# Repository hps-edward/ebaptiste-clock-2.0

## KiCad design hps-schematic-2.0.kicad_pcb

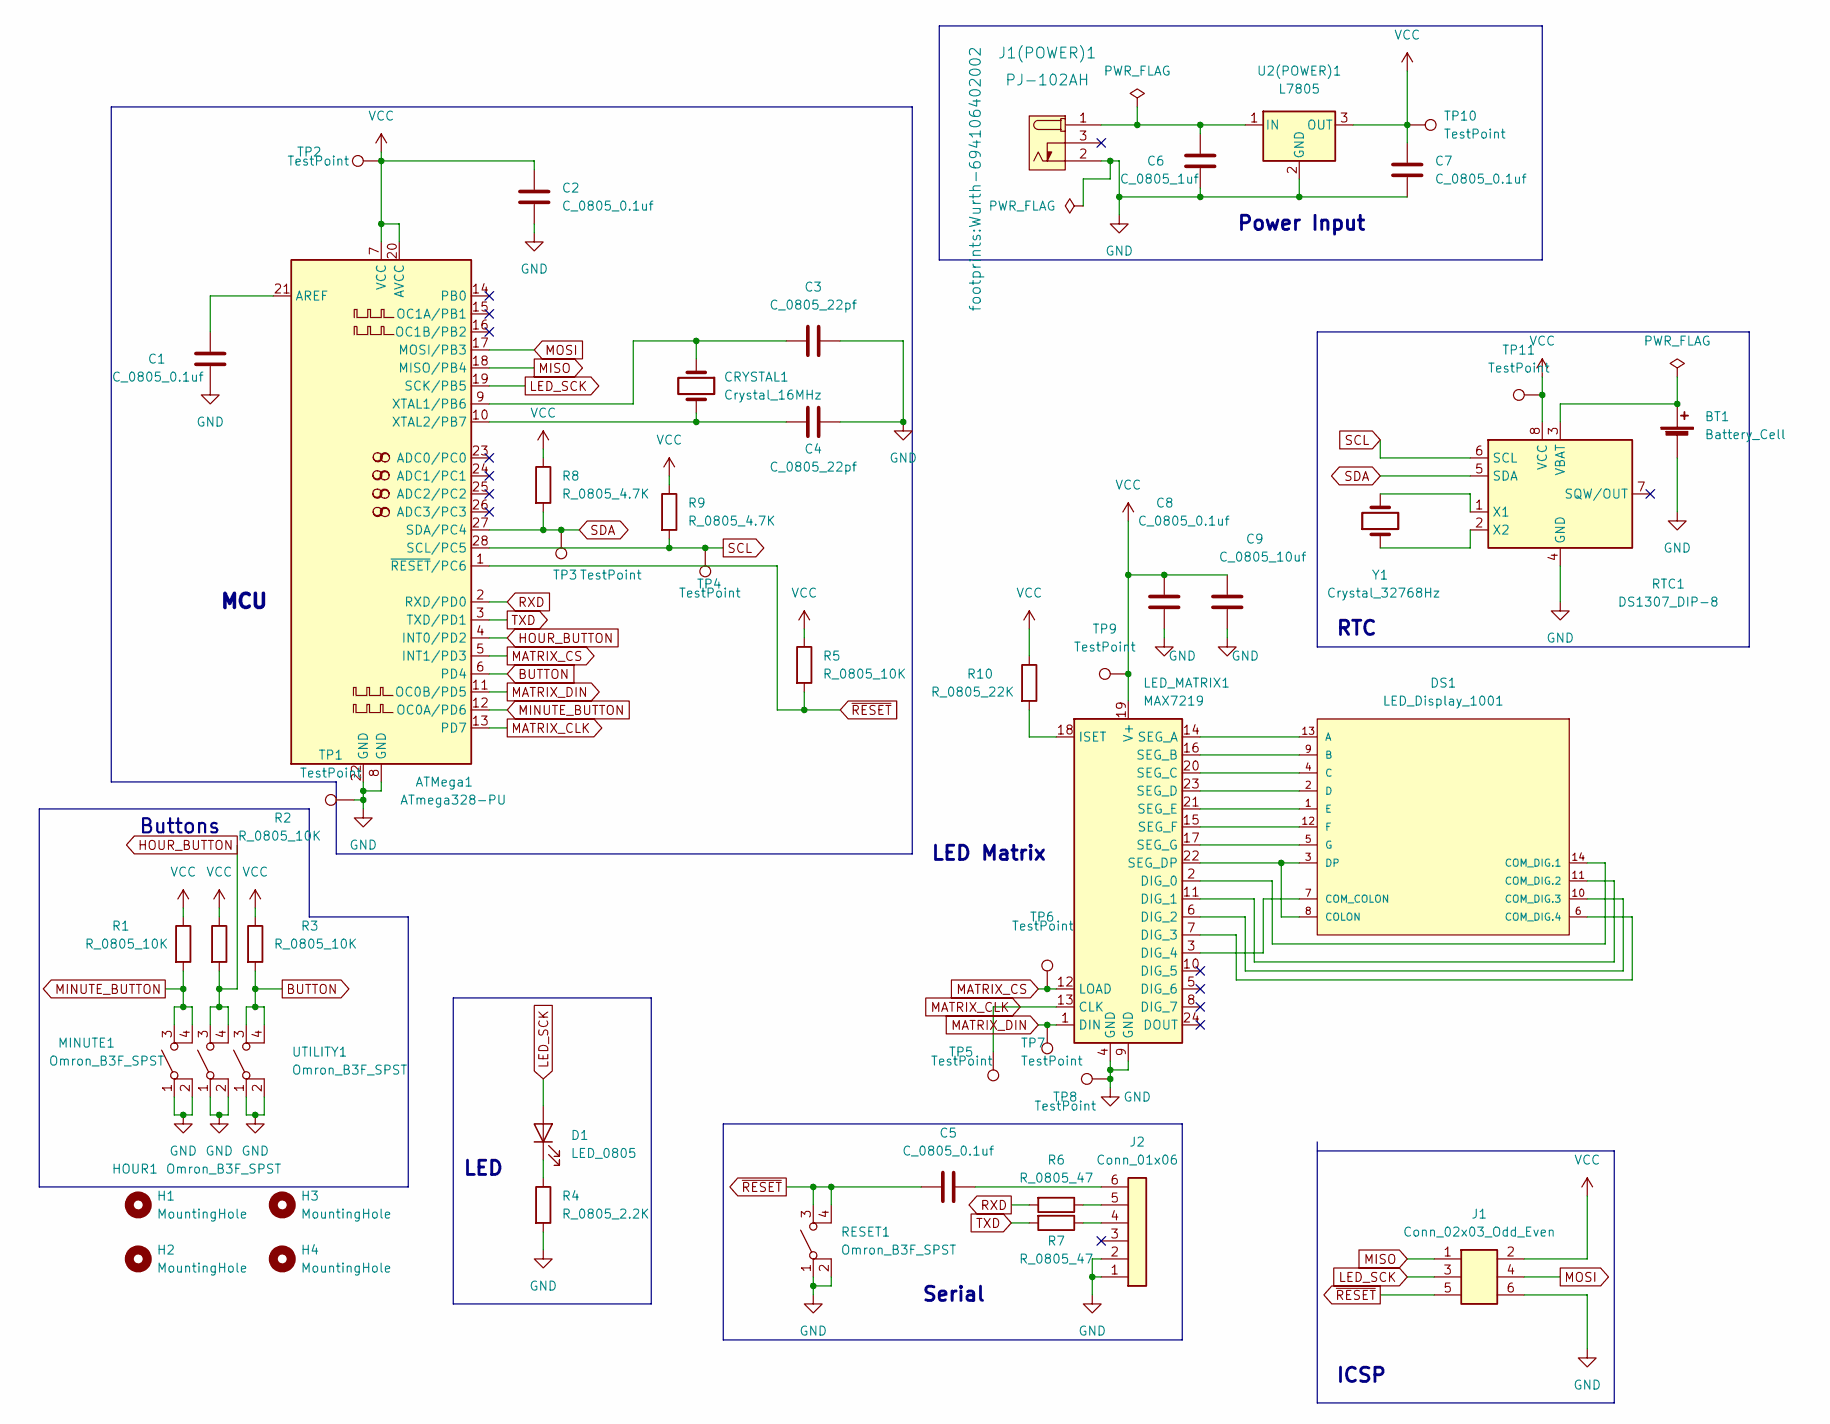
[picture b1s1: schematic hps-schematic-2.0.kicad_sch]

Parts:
ATMega1: ATmega328-PU; DIP-28_W7.62mm; MPN ED281DT; Digikey PN ED3050-5-ND
BT1: Battery_Cell; BatteryHolder_Keystone_106_1x20mm; MPN BS-7; Digikey PN BS-7-ND
C1, C2, C5, C7, C8: C_0805_0.1uf; C_0805_2012Metric; Voltage N/A; Tolerance N/A; MPN 08055C104KAT2A; Digikey PN 478-1395-1-ND
C3, C4: C_0805_22pf; C_0805_2012Metric; Voltage N/A; Tolerance N/A; MPN CC0805JRNPO9BN220; Digikey PN 311-1103-1-ND
C6: C_0805_1uf; C_0805_2012Metric; Voltage N/A; Tolerance N/A; MPN CC0805KKX7R8BB105; Digikey PN 311-1456-1-ND
C9: C_0805_10uf; C_0805_2012Metric; Voltage N/A; Tolerance N/A; MPN GRM21BR61E106KA73L; Digikey PN 490-5523-1-ND
CRYSTAL1: Crystal_16MHz; Crystal_SMD_HC49-SD; MPN ECS-160-20-5PXDN-TR; Digikey PN XC1299CT-ND
D1: LED_0805; LED_0805_2012Metric; MPN 150080RS75000; Digikey PN 732-4984-1-ND
DS1: LED_Display_1001; Adafruit-1001-0-0-MFG; forward voltage 3.2V; reverse voltage 5V; mouser part number 485-1001; digikey description WHITE 7-SEGMENT CLOCK DISPLAY
H1, H2, H3, H4: MountingHole; MountingHole_3.2mm_M3
HOUR1: Omron_B3F_SPST; SW_SPST_Omron_B3FS-100xP; MPN B3FS-1000P; Digikey PN SW423CT-ND
J1: Conn_02x03_Odd_Even; PinHeader_2x03_P2.54mm_Vertical; MPN PRPC003DAAN-RC; Digikey PN S2011EC-03-ND
J1(POWER)1: PJ-102AH; Wurth-694106402002; MPN 694106402002; Digikey PN 732-5931-ND
J2: Conn_01x06; PinHeader_1x06_P2.54mm_Vertical; MPN 61300611121; Digikey PN 732-5319-ND
LED_MATRIX1: MAX7219; DIP-24_W7.62mm; MPN ED241DT; Digikey PN ED3049-5-ND
MINUTE1: Omron_B3F_SPST; SW_SPST_Omron_B3FS-100xP; MPN B3FS-1000P; Digikey PN SW423CT-ND
R1, R2, R3, R5: R_0805_10K; R_0805_2012Metric; Tolerance N/A; MPN RC0805FR-0710KL; Digikey PN 311-10.0KCRCT-ND
R4: R_0805_2.2K; R_0805_2012Metric; Tolerance N/A; MPN N/A; Digikey PN 311-2.20KCRCT-ND
R6, R7: R_0805_47; R_0805_2012Metric; Tolerance N/A; Mouser PN N/A; Digikey PN RC0805FR-0747RL
R8, R9: R_0805_4.7K; R_0805_2012Metric; Tolerance N/A; MPN RC0805FR-074K7L; Digikey PN 311-4.70KCRCT-ND
R10: R_0805_22K; R_0805_2012Metric; Tolerance N/A; MPN RC0805FR-0722KL; Digikey PN 311-22.0KCRCT-ND
RESET1: Omron_B3F_SPST; SW_SPST_Omron_B3FS-100xP; MPN B3FS-1000P; Digikey PN SW423CT-ND
RTC1: DS1307_DIP-8; DIP-8_W7.62mm; MPN A 08-LC-TT; Digikey PN AE9986-ND
TP1, TP2, TP3, TP4, TP5, TP6, TP7, TP8, TP9, TP10, TP11: TestPoint; TestPoint_THTPad_D2.0mm_Drill1.0mm
U2(POWER)1: L7805; TO-252-2; MPN L7805CDT-TR; Digikey PN 497-7255-1-ND
UTILITY1: Omron_B3F_SPST; SW_SPST_Omron_B3FS-100xP; MPN B3FS-1000P; Digikey PN SW423CT-ND
Y1: Crystal_32768Hz; Crystal_SMD_2Pin_3.2x1.5mm; MPN Q 0,032768-JTX310-12,5-20-T1-HMR-50K-LF; Digikey PN 1908-1314-1-ND

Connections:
BUTTON: ATMega1.6 (PD4), R3.2, UTILITY1.3 (B), UTILITY1.4 (B)
GND: ATMega1.8 (GND), ATMega1.22 (GND), BT1.2 (-), C1.2, C2.2, C3.1, C4.1, C6.2, C7.2, C8.2, C9.2, HOUR1.1 (A), HOUR1.2 (A), J1.6, J1(POWER)1.2 (OUT), J2.1, J2.2, LED_MATRIX1.4 (GND), LED_MATRIX1.9 (GND), MINUTE1.1 (A), MINUTE1.2 (A), R4.2, RESET1.1 (A), RESET1.2 (A), RTC1.4 (GND), TP1.1, TP8.1, U2(POWER)1.2 (GND), UTILITY1.1 (A), UTILITY1.2 (A)
HOUR_BUTTON: ATMega1.4 (INT0/PD2), HOUR1.3 (B), HOUR1.4 (B), R2.2
LED_SCK: ATMega1.19 (SCK/PB5), D1.2 (A), J1.3
MATRIX_CLK: ATMega1.13 (PD7), LED_MATRIX1.13 (CLK), TP5.1
MATRIX_CS: ATMega1.5 (INT1/PD3), LED_MATRIX1.12 (LOAD), TP6.1
MATRIX_DIN: ATMega1.11 (OC0B/PD5), LED_MATRIX1.1 (DIN), TP7.1
MINUTE_BUTTON: ATMega1.12 (OC0A/PD6), MINUTE1.3 (B), MINUTE1.4 (B), R1.2
MISO: ATMega1.18 (MISO/PB4), J1.1
MOSI: ATMega1.17 (MOSI/PB3), J1.4
unnamed: ATMega1.9 (XTAL1/PB6), C3.2, CRYSTAL1.1
unnamed: ATMega1.10 (XTAL2/PB7), C4.2, CRYSTAL1.2
unnamed: ATMega1.21 (AREF), C1.1
unnamed: BT1.1 (+), RTC1.3 (VBAT)
unnamed: C5.2, J2.6
unnamed: C6.1, J1(POWER)1.1 (POLE), U2(POWER)1.1 (IN)
unnamed: D1.1 (K), R4.1
unnamed: DS1.1 (E), LED_MATRIX1.21 (SEG_E)
unnamed: DS1.2 (D), LED_MATRIX1.23 (SEG_D)
unnamed: DS1.3 (DP), DS1.8 (COLON), LED_MATRIX1.22 (SEG_DP)
unnamed: DS1.4 (C), LED_MATRIX1.20 (SEG_C)
unnamed: DS1.5 (G), LED_MATRIX1.17 (SEG_G)
unnamed: DS1.6 (COM_DIG.4), LED_MATRIX1.7 (DIG_3)
unnamed: DS1.7 (COM_COLON), LED_MATRIX1.3 (DIG_4)
unnamed: DS1.9 (B), LED_MATRIX1.16 (SEG_B)
unnamed: DS1.10 (COM_DIG.3), LED_MATRIX1.6 (DIG_2)
unnamed: DS1.11 (COM_DIG.2), LED_MATRIX1.11 (DIG_1)
unnamed: DS1.12 (F), LED_MATRIX1.15 (SEG_F)
unnamed: DS1.13 (A), LED_MATRIX1.14 (SEG_A)
unnamed: DS1.14 (COM_DIG.1), LED_MATRIX1.2 (DIG_0)
unnamed: J2.4, R7.1
unnamed: J2.5, R6.1
unnamed: LED_MATRIX1.18 (ISET), R10.2
unnamed: RTC1.1 (X1), Y1.2
unnamed: RTC1.2 (X2), Y1.1
RXD: ATMega1.2 (RXD/PD0), R6.2
SCL: ATMega1.28 (SCL/PC5), R9.2, RTC1.6 (SCL), TP4.1
SDA: ATMega1.27 (SDA/PC4), R8.2, RTC1.5 (SDA), TP3.1
TXD: ATMega1.3 (TXD/PD1), R7.2
VCC: ATMega1.7 (VCC), ATMega1.20 (AVCC), C2.1, C7.1, C8.1, C9.1, J1.2, LED_MATRIX1.19 (V+), R1.1, R2.1, R3.1, R5.1, R8.1, R9.1, R10.1, RTC1.8 (VCC), TP2.1, TP9.1, TP10.1, TP11.1, U2(POWER)1.3 (OUT)
~RESET: ATMega1.1 (~RESET/PC6), C5.1, J1.5, R5.2, RESET1.3 (B), RESET1.4 (B)

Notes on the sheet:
ICSP
Buttons
Serial
LED Matrix
Power Input
MCU
LED
RTC

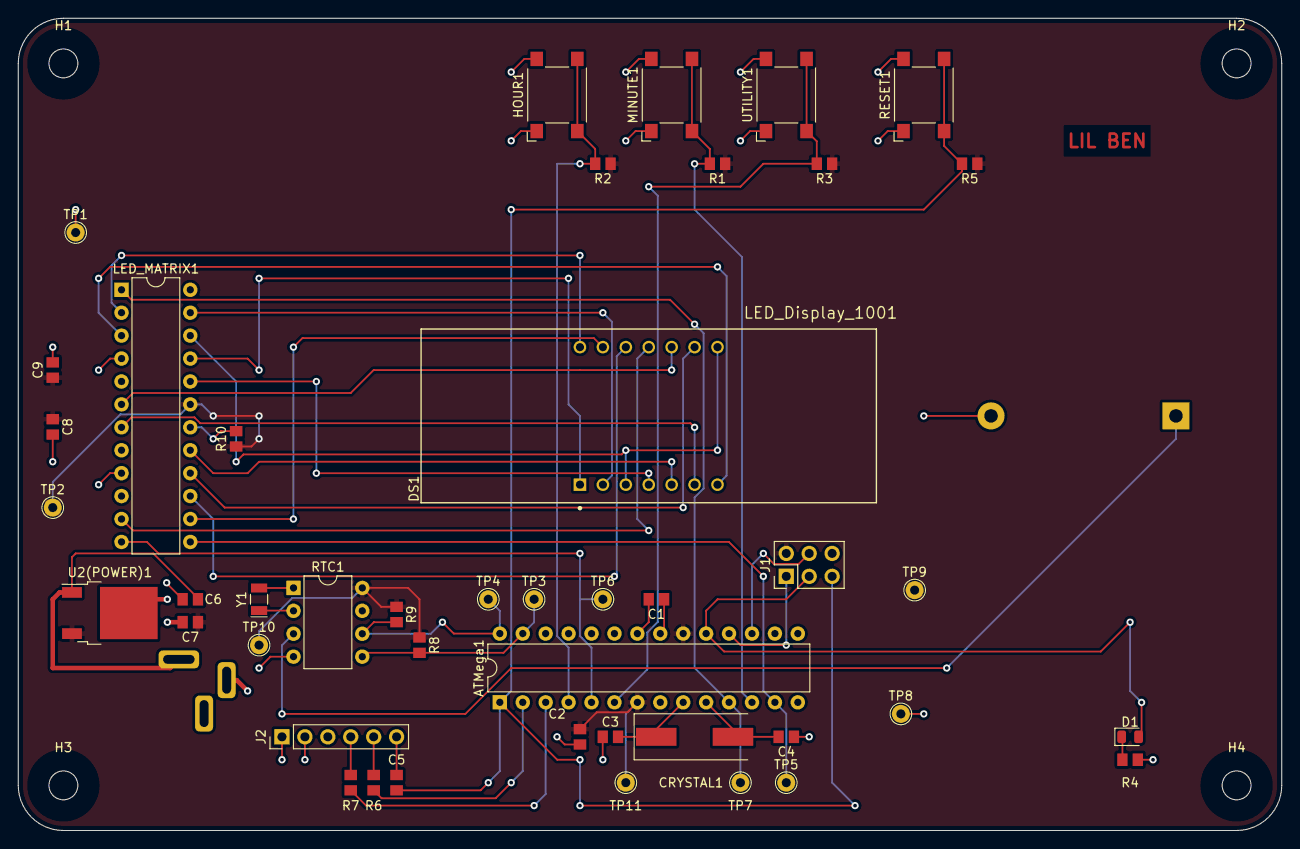
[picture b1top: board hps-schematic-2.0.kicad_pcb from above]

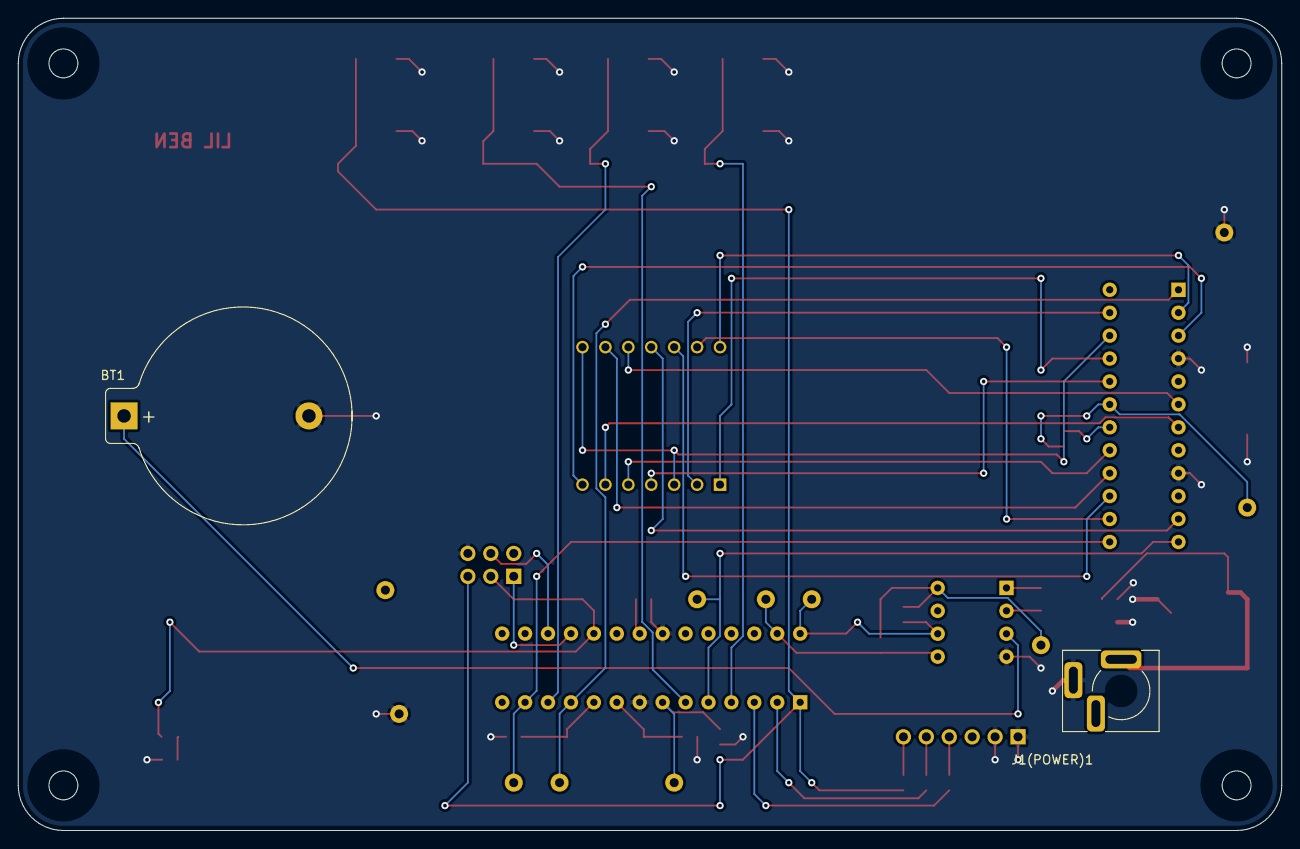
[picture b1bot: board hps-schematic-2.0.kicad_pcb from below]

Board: 2 copper layers, 140.0 x 90.0 mm, 50 parts (2 on the bottom side), 41 nets.

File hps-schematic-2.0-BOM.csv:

"Id";"Designator";"Package";"Quantity";"Designation";"Supplier and ref";
1;"R6,R7";"R_0805_2012Metric";2;"R_0805_47";;;
2;"H4,H2,H3,H1";"MountingHole_3.2mm_M3";4;"MountingHole";;;
3;"C3,C4";"C_0805_2012Metric";2;"C_0805_22pf";;;
4;"C7,C1,C5,C8,C2";"C_0805_2012Metric";5;"C_0805_0.1uf";;;
5;"R10";"R_0805_2012Metric";1;"R_0805_22K";;;
6;"R3,R1,R5,R2";"R_0805_2012Metric";4;"R_0805_10K";;;
7;"R4";"R_0805_2012Metric";1;"R_0805_2.2K";;;
8;"U2(POWER)1";"TO-252-2";1;"L7805";;;
9;"LED_MATRIX1";"DIP-24_W7.62mm";1;"MAX7219";;;
10;"RTC1";"DIP-8_W7.62mm";1;"DS1307_DIP-8";;;
11;"TP8,TP4,TP9,TP6,TP2,TP10,TP7,TP1,TP3,TP5,TP11";"TestPoint_THTPad_D2.0mm_Drill1.0mm";11;"TestPoint";;;
12;"R8,R9";"R_0805_2012Metric";2;"R_0805_4.7K";;;
13;"C9";"C_0805_2012Metric";1;"C_0805_10uf";;;
14;"J2";"PinHeader_1x06_P2.54mm_Vertical";1;"Conn_01x06";;;
15;"HOUR1,UTILITY1,RESET1,MINUTE1";"SW_SPST_Omron_B3FS-100xP";4;"Omron_B3F_SPST";;;
16;"ATMega1";"DIP-28_W7.62mm";1;"ATmega328-PU";;;
17;"J1";"PinHeader_2x03_P2.54mm_Vertical";1;"Conn_02x03_Odd_Even";;;
18;"D1";"LED_0805_2012Metric";1;"LED_0805";;;
19;"DS1";"Adafruit-1001-0-0-MFG";1;"LED_Display_1001";;;
20;"Y1";"Crystal_SMD_2Pin_3.2x1.5mm";1;"Crystal_32768Hz";;;
21;"C6";"C_0805_2012Metric";1;"C_0805_1uf";;;
22;"CRYSTAL1";"Crystal_SMD_HC49-SD";1;"Crystal_16MHz";;;
23;"J1(POWER)1";"Wurth-694106402002";1;"PJ-102AH";;;
24;"BT1";"BatteryHolder_Keystone_106_1x20mm";1;"Battery_Cell";;;

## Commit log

2022-07-22 Schematic/PCB Update
2022-07-22 Gerber Out
2022-07-25 Gerber Out 2.0
